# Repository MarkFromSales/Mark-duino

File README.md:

# Mark-duino
Playing around with my own Arduino build, purely academic really. Basically I wanted to keep the same setup as a typical Arduino Nano but expand the GPIO dramatically. The MCP23017-E/SP is used a lot in my other projects and works very well for my hobbyist needs.

## Attributions and Thanks
- ATMega328 outside of Arduino Uno - https://dronebotworkshop.com/arduino-uno-atmega328/
- Multi-tasking the Arduino - https://learn.adafruit.com/multi-tasking-the-arduino-part-1?view=all
- MCP23017 I2C GPIO expander - https://www.adafruit.com/product/732
- KiCad tutorials and much more - https://contextualelectronics.com/
- KiCad interactive BOM tool video - https://www.youtube.com/watch?v=H9WsmhtoH8E
- KiCad interactive BOM tool location - https://github.com/openscopeproject/InteractiveHtmlBom

## Bill of Materials
Important note: I chose many of these components because I already had a pile of them from other projects. The 100nF capacitor on C1 is a great example of where I had an existing part and chose that over a better, more consistent footprint. Later version of this project will use more consistent (mostly 1206) footprints.

The screw terminals drive the overall price of the project fairly high if you don't already have these on hand. Substitute them out with a regular 2.54mm pin header or socket strips to cut cost if desired.

You can import this CSV directly into Digi-Key (www.digikey.com)
https://github.com/MarkFromSales/Mark-duino/blob/master/mark-duino_bom.csv

## MCP Addresses
The MCP A0, A1, and A2 pins are not directly connected in the PCB and have solder jumpers instead to allow flexibility in addressing. 

```
addr 0 = A2 low,  A1 low,  A0 low  000
addr 1 = A2 low,  A1 low,  A0 high 001
addr 2 = A2 low,  A1 high, A0 low  010
addr 3 = A2 low,  A1 high, A0 high 011
addr 4 = A2 high, A1 low,  A0 low  100
addr 5 = A2 high, A1 low,  A0 high 101
addr 6 = A2 high, A1 high, A0 low  110
addr 7 = A2 high, A1 high, A0 high 111
```

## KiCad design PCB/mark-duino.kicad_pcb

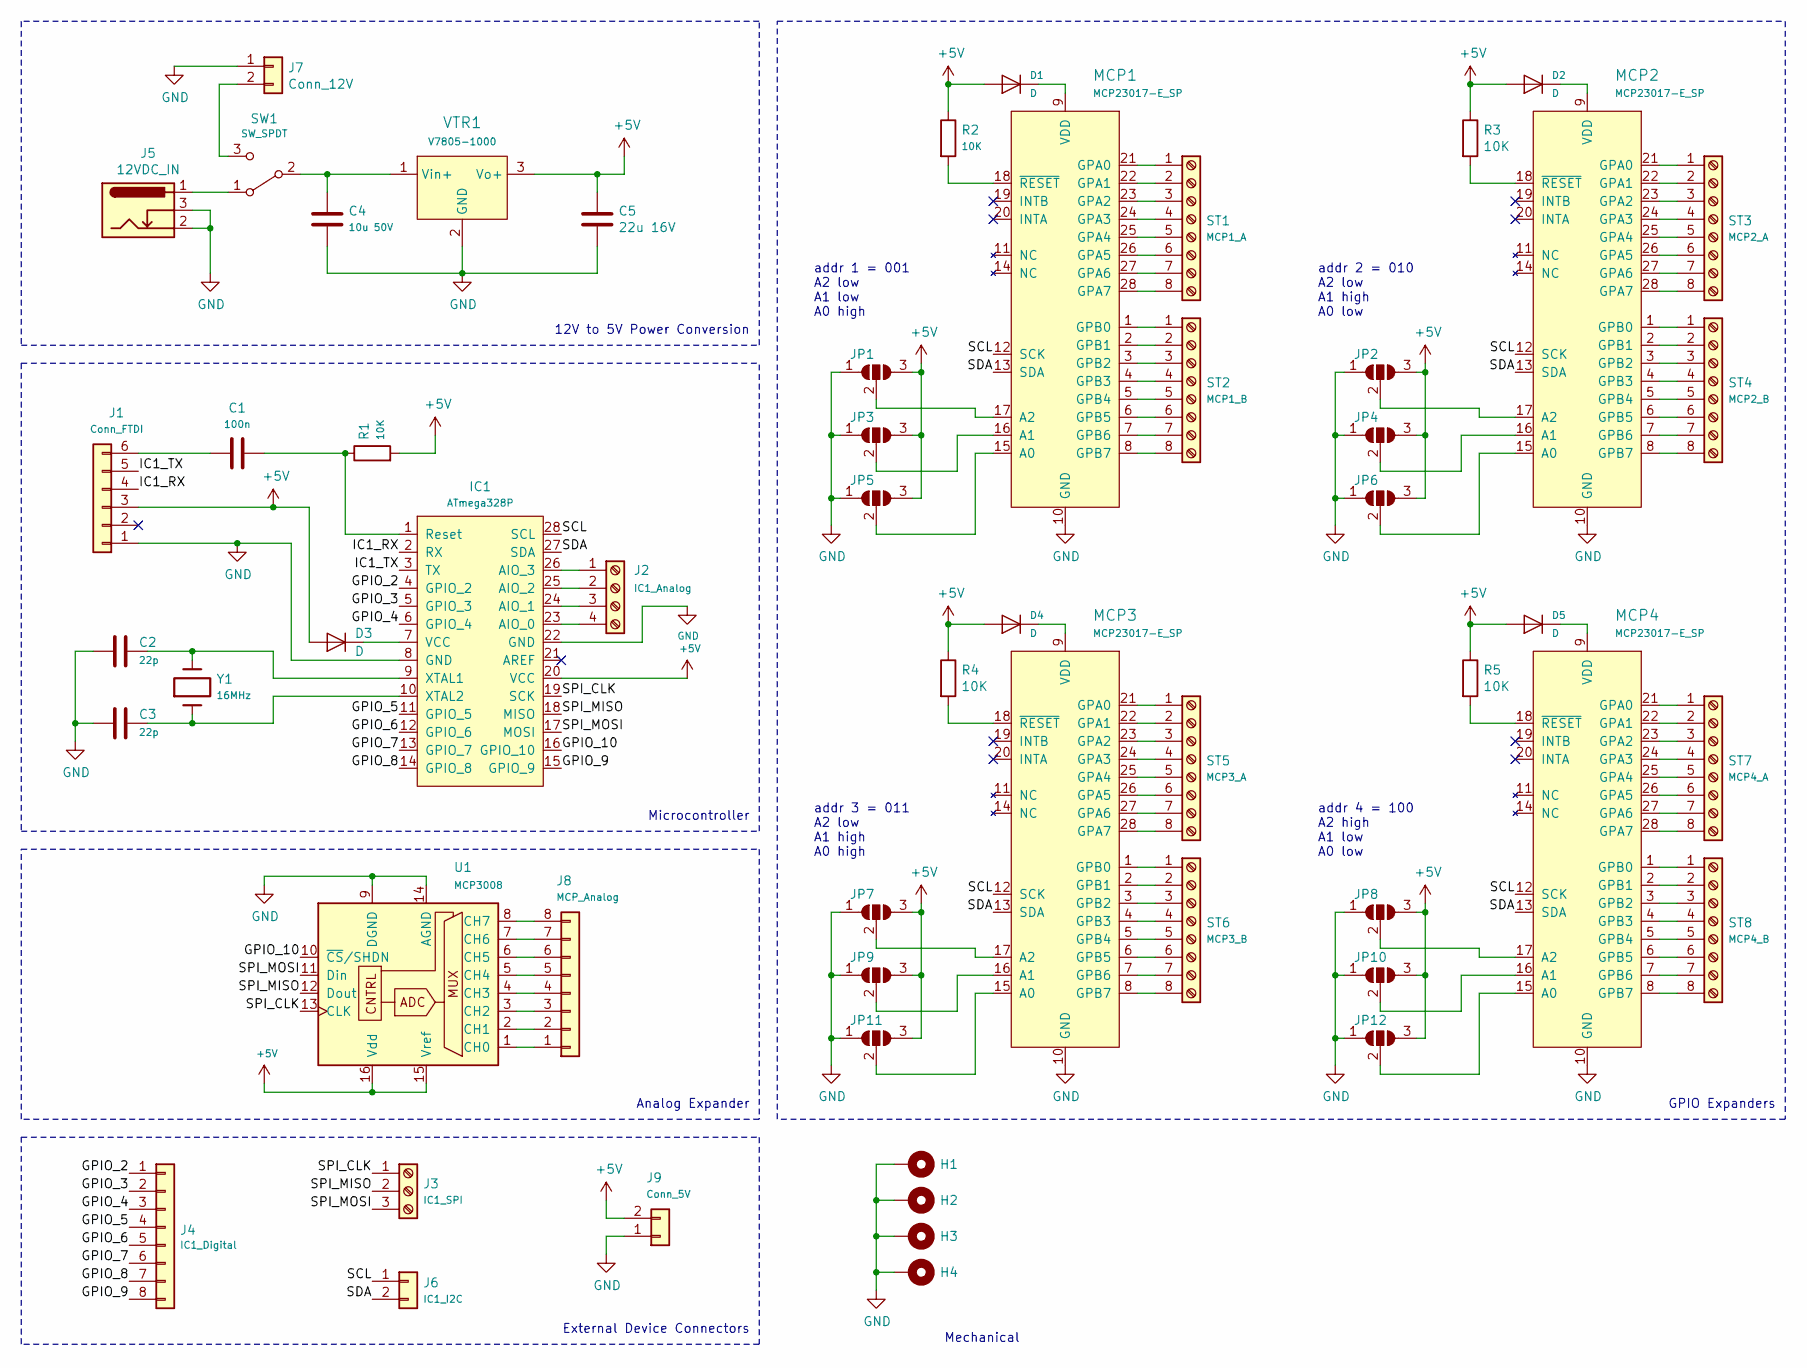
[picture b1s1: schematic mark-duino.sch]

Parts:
C1: 100n; C_Disc_D10.5mm_W5.0mm_P7.50mm
C2, C3: 22p; C_0805_2012Metric_Pad1.15x1.40mm_HandSolder
C4: 10u 50V; C_1206_3216Metric_Pad1.42x1.75mm_HandSolder
C5: 22u 16V; C_1206_3216Metric_Pad1.42x1.75mm_HandSolder
D1, D2, D3, D4, D5: D; D_0805_2012Metric_Pad1.15x1.40mm_HandSolder
H1, H2, H3, H4: MountingHole_Pad; MountingHole_3.2mm_M3_Pad
IC1: ATmega328P; DIP-28_W7.62mm_Socket
J1: Conn_FTDI; PinHeader_1x06_P2.54mm_Vertical
J2: IC1_Analog; PinHeader_1x04_P2.54mm_Vertical
J3: IC1_SPI; PinHeader_1x03_P2.54mm_Vertical
J4: IC1_Digital; PinHeader_1x08_P2.54mm_Vertical
J5: 12VDC_IN; BarrelJack_CUI_PJ-102AH_Horizontal
J6: IC1_I2C; PinHeader_1x02_P2.54mm_Vertical
J7: Conn_12V; JST_XH_B02B-XH-A_1x02_P2.50mm_Vertical
J8: MCP_Analog; PinHeader_1x08_P2.54mm_Vertical
J9: Conn_5V; PinHeader_1x02_P2.54mm_Vertical
JP1, JP2, JP3, JP4, JP5, JP6, JP7, JP8, JP9, JP10, JP11, JP12: SolderJumper_3_Open; SolderJumper-3_P1.3mm_Open_RoundedPad1.0x1.5mm_NumberLabels
MCP1, MCP2, MCP3, MCP4: MCP23017-E_SP; DIP-28_W7.62mm; MPN MCP23017-E/SP; Digi-Key_PN MCP23017-E/SP-ND
R1, R2, R3, R4, R5: 10K; C_1206_3216Metric_Pad1.42x1.75mm_HandSolder
ST1: MCP1_A; TerminalBlock_TE_282834-8_1x08_P2.54mm_Horizontal
ST2: MCP1_B; TerminalBlock_TE_282834-8_1x08_P2.54mm_Horizontal
ST3: MCP2_A; TerminalBlock_TE_282834-8_1x08_P2.54mm_Horizontal
ST4: MCP2_B; TerminalBlock_TE_282834-8_1x08_P2.54mm_Horizontal
ST5: MCP3_A; TerminalBlock_TE_282834-8_1x08_P2.54mm_Horizontal
ST6: MCP3_B; TerminalBlock_TE_282834-8_1x08_P2.54mm_Horizontal
ST7: MCP4_A; TerminalBlock_TE_282834-8_1x08_P2.54mm_Horizontal
ST8: MCP4_B; TerminalBlock_TE_282834-8_1x08_P2.54mm_Horizontal
SW1: SW_SPDT; SW_E-Switch_EG1224_SPDT_Angled
U1: MCP3008; DIP-16_W7.62mm
VTR1: V7805-1000; 3-SIP_Module_V7805-1000; MPN V7805-1000; Digi-Key_PN 102-1715-ND
Y1: 16MHz; Resonator-2Pin_W10.0mm_H5.0mm

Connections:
/GPIO_2: IC1.4 (GPIO_2), J4.1
/GPIO_3: IC1.5 (GPIO_3), J4.2
/GPIO_4: IC1.6 (GPIO_4), J4.3
/GPIO_5: IC1.11 (GPIO_5), J4.4
/GPIO_6: IC1.12 (GPIO_6), J4.5
/GPIO_7: IC1.13 (GPIO_7), J4.6
/GPIO_8: IC1.14 (GPIO_8), J4.7
/GPIO_9: IC1.15 (GPIO_9), J4.8
/GPIO_10: IC1.16 (GPIO_10), U1.10 (~CS~/SHDN)
/IC1_RX: IC1.2 (RX), J1.4
/IC1_TX: IC1.3 (TX), J1.5
/SCL: IC1.28 (SCL), J6.1, MCP1.12 (SCK), MCP2.12 (SCK), MCP3.12 (SCK), MCP4.12 (SCK)
/SDA: IC1.27 (SDA), J6.2, MCP1.13 (SDA), MCP2.13 (SDA), MCP3.13 (SDA), MCP4.13 (SDA)
/SPI_CLK: IC1.19 (SCK), J3.1, U1.13 (CLK)
/SPI_MISO: IC1.18 (MISO), J3.2, U1.12 (Dout)
/SPI_MOSI: IC1.17 (MOSI), J3.3, U1.11 (Din)
GND: C2.2, C3.2, C4.2, C5.2, H1.1, H2.1, H3.1, H4.1, IC1.8 (GND), IC1.22 (GND), J1.1, J5.2, J5.3, J7.1, J9.1, JP1.1 (A), JP2.1 (A), JP3.1 (A), JP4.1 (A), JP5.1 (A), JP6.1 (A), JP7.1 (A), JP8.1 (A), JP9.1 (A), JP10.1 (A), JP11.1 (A), JP12.1 (A), MCP1.10 (GND), MCP2.10 (GND), MCP3.10 (GND), MCP4.10 (GND), U1.9 (DGND), U1.14 (AGND), VTR1.2 (GND)
unnamed: C1.2, J1.6
unnamed: C2.1, IC1.9 (XTAL1), Y1.2
unnamed: C3.1, IC1.10 (XTAL2), Y1.1
unnamed: C4.1, SW1.2 (B), VTR1.1 (Vin+)
unnamed: D1.1 (K), MCP1.9 (VDD)
unnamed: D2.1 (K), MCP2.9 (VDD)
unnamed: D3.1 (K), IC1.7 (VCC)
unnamed: D4.1 (K), MCP3.9 (VDD)
unnamed: D5.1 (K), MCP4.9 (VDD)
unnamed: IC1.23 (AIO_0), J2.4
unnamed: IC1.24 (AIO_1), J2.3
unnamed: IC1.25 (AIO_2), J2.2
unnamed: IC1.26 (AIO_3), J2.1
unnamed: J5.1, SW1.1 (A)
unnamed: J7.2, SW1.3 (C)
unnamed: J8.1, U1.1 (CH0)
unnamed: J8.2, U1.2 (CH1)
unnamed: J8.3, U1.3 (CH2)
unnamed: J8.4, U1.4 (CH3)
unnamed: J8.5, U1.5 (CH4)
unnamed: J8.6, U1.6 (CH5)
unnamed: J8.7, U1.7 (CH6)
unnamed: J8.8, U1.8 (CH7)
unnamed: JP1.2 (C), MCP1.17 (A2)
unnamed: JP2.2 (C), MCP2.17 (A2)
unnamed: JP3.2 (C), MCP1.16 (A1)
unnamed: JP4.2 (C), MCP2.16 (A1)
unnamed: JP5.2 (C), MCP1.15 (A0)
unnamed: JP6.2 (C), MCP2.15 (A0)
unnamed: JP7.2 (C), MCP3.17 (A2)
unnamed: JP8.2 (C), MCP4.17 (A2)
unnamed: JP9.2 (C), MCP3.16 (A1)
unnamed: JP10.2 (C), MCP4.16 (A1)
unnamed: JP11.2 (C), MCP3.15 (A0)
unnamed: JP12.2 (C), MCP4.15 (A0)
unnamed: MCP1.1 (GPB0), ST2.1
unnamed: MCP1.2 (GPB1), ST2.2
unnamed: MCP1.3 (GPB2), ST2.3
unnamed: MCP1.4 (GPB3), ST2.4
unnamed: MCP1.5 (GPB4), ST2.5
unnamed: MCP1.6 (GPB5), ST2.6
unnamed: MCP1.7 (GPB6), ST2.7
unnamed: MCP1.8 (GPB7), ST2.8
unnamed: MCP1.18 (~RESET), R2.2
unnamed: MCP1.21 (GPA0), ST1.1
unnamed: MCP1.22 (GPA1), ST1.2
unnamed: MCP1.23 (GPA2), ST1.3
unnamed: MCP1.24 (GPA3), ST1.4
unnamed: MCP1.25 (GPA4), ST1.5
unnamed: MCP1.26 (GPA5), ST1.6
unnamed: MCP1.27 (GPA6), ST1.7
unnamed: MCP1.28 (GPA7), ST1.8
unnamed: MCP2.1 (GPB0), ST4.1
unnamed: MCP2.2 (GPB1), ST4.2
unnamed: MCP2.3 (GPB2), ST4.3
unnamed: MCP2.4 (GPB3), ST4.4
unnamed: MCP2.5 (GPB4), ST4.5
unnamed: MCP2.6 (GPB5), ST4.6
unnamed: MCP2.7 (GPB6), ST4.7
unnamed: MCP2.8 (GPB7), ST4.8
unnamed: MCP2.18 (~RESET), R3.2
unnamed: MCP2.21 (GPA0), ST3.1
unnamed: MCP2.22 (GPA1), ST3.2
unnamed: MCP2.23 (GPA2), ST3.3
unnamed: MCP2.24 (GPA3), ST3.4
unnamed: MCP2.25 (GPA4), ST3.5
unnamed: MCP2.26 (GPA5), ST3.6
unnamed: MCP2.27 (GPA6), ST3.7
unnamed: MCP2.28 (GPA7), ST3.8
unnamed: MCP3.1 (GPB0), ST6.1
unnamed: MCP3.2 (GPB1), ST6.2
unnamed: MCP3.3 (GPB2), ST6.3
unnamed: MCP3.4 (GPB3), ST6.4
unnamed: MCP3.5 (GPB4), ST6.5
unnamed: MCP3.6 (GPB5), ST6.6
unnamed: MCP3.7 (GPB6), ST6.7
unnamed: MCP3.8 (GPB7), ST6.8
unnamed: MCP3.18 (~RESET), R4.2
unnamed: MCP3.21 (GPA0), ST5.1
unnamed: MCP3.22 (GPA1), ST5.2
unnamed: MCP3.23 (GPA2), ST5.3
unnamed: MCP3.24 (GPA3), ST5.4
unnamed: MCP3.25 (GPA4), ST5.5
unnamed: MCP3.26 (GPA5), ST5.6
unnamed: MCP3.27 (GPA6), ST5.7
unnamed: MCP3.28 (GPA7), ST5.8
unnamed: MCP4.1 (GPB0), ST8.1
unnamed: MCP4.2 (GPB1), ST8.2
unnamed: MCP4.3 (GPB2), ST8.3
unnamed: MCP4.4 (GPB3), ST8.4
unnamed: MCP4.5 (GPB4), ST8.5
unnamed: MCP4.6 (GPB5), ST8.6
unnamed: MCP4.7 (GPB6), ST8.7
unnamed: MCP4.8 (GPB7), ST8.8
unnamed: MCP4.18 (~RESET), R5.2
unnamed: MCP4.21 (GPA0), ST7.1
unnamed: MCP4.22 (GPA1), ST7.2
unnamed: MCP4.23 (GPA2), ST7.3
unnamed: MCP4.24 (GPA3), ST7.4
unnamed: MCP4.25 (GPA4), ST7.5
unnamed: MCP4.26 (GPA5), ST7.6
unnamed: MCP4.27 (GPA6), ST7.7
unnamed: MCP4.28 (GPA7), ST7.8

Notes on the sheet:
GPIO Expanders
12V to 5V Power Conversion
Microcontroller
Analog Expander
External Device Connectors
Mechanical
addr 1 = 001 A2 low A1 low A0 high
addr 2 = 010 A2 low A1 high A0 low
addr 3 = 011 A2 low A1 high A0 high
addr 4 = 100 A2 high A1 low A0 low

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
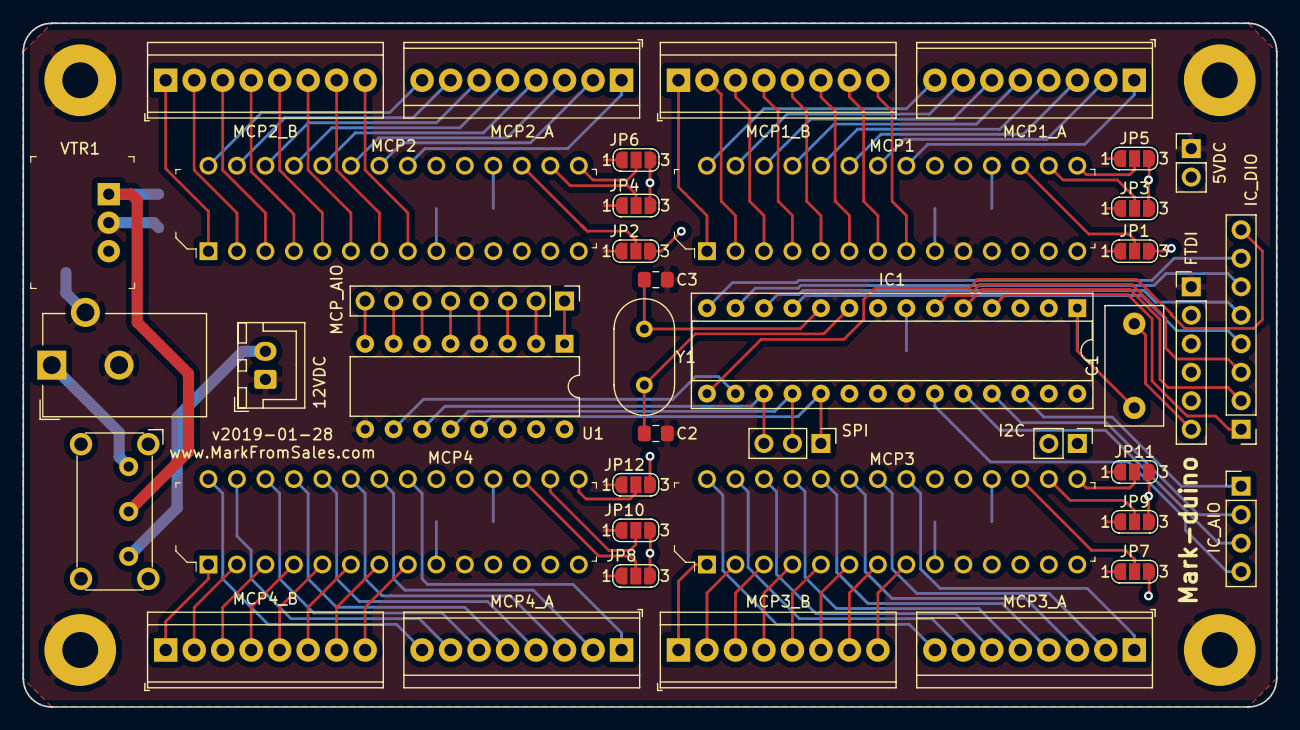
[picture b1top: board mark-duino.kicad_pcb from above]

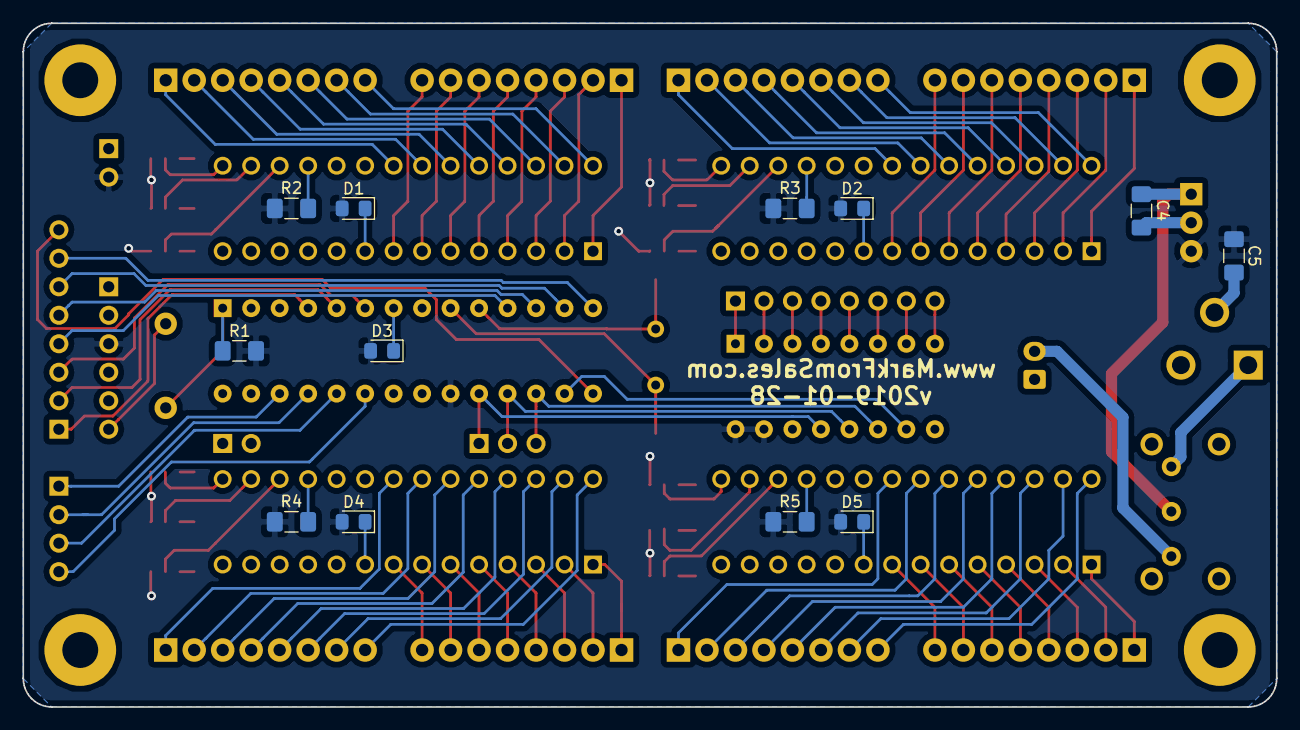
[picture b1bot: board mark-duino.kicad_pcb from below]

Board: 4 copper layers, 111.8 x 61.0 mm, 57 parts (12 on the bottom side), 122 nets.

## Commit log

2019-02-02 Initial upload
2019-02-03 web friendly exports
2019-02-03 Added files
2019-02-03 Cleaned up and updated documentation
2019-02-09 Rounded corners
2019-02-13 Updated structure
